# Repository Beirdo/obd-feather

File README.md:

# obd-feather
OBDII interface board with an attached Adafruit STM32F405 Feather Express.

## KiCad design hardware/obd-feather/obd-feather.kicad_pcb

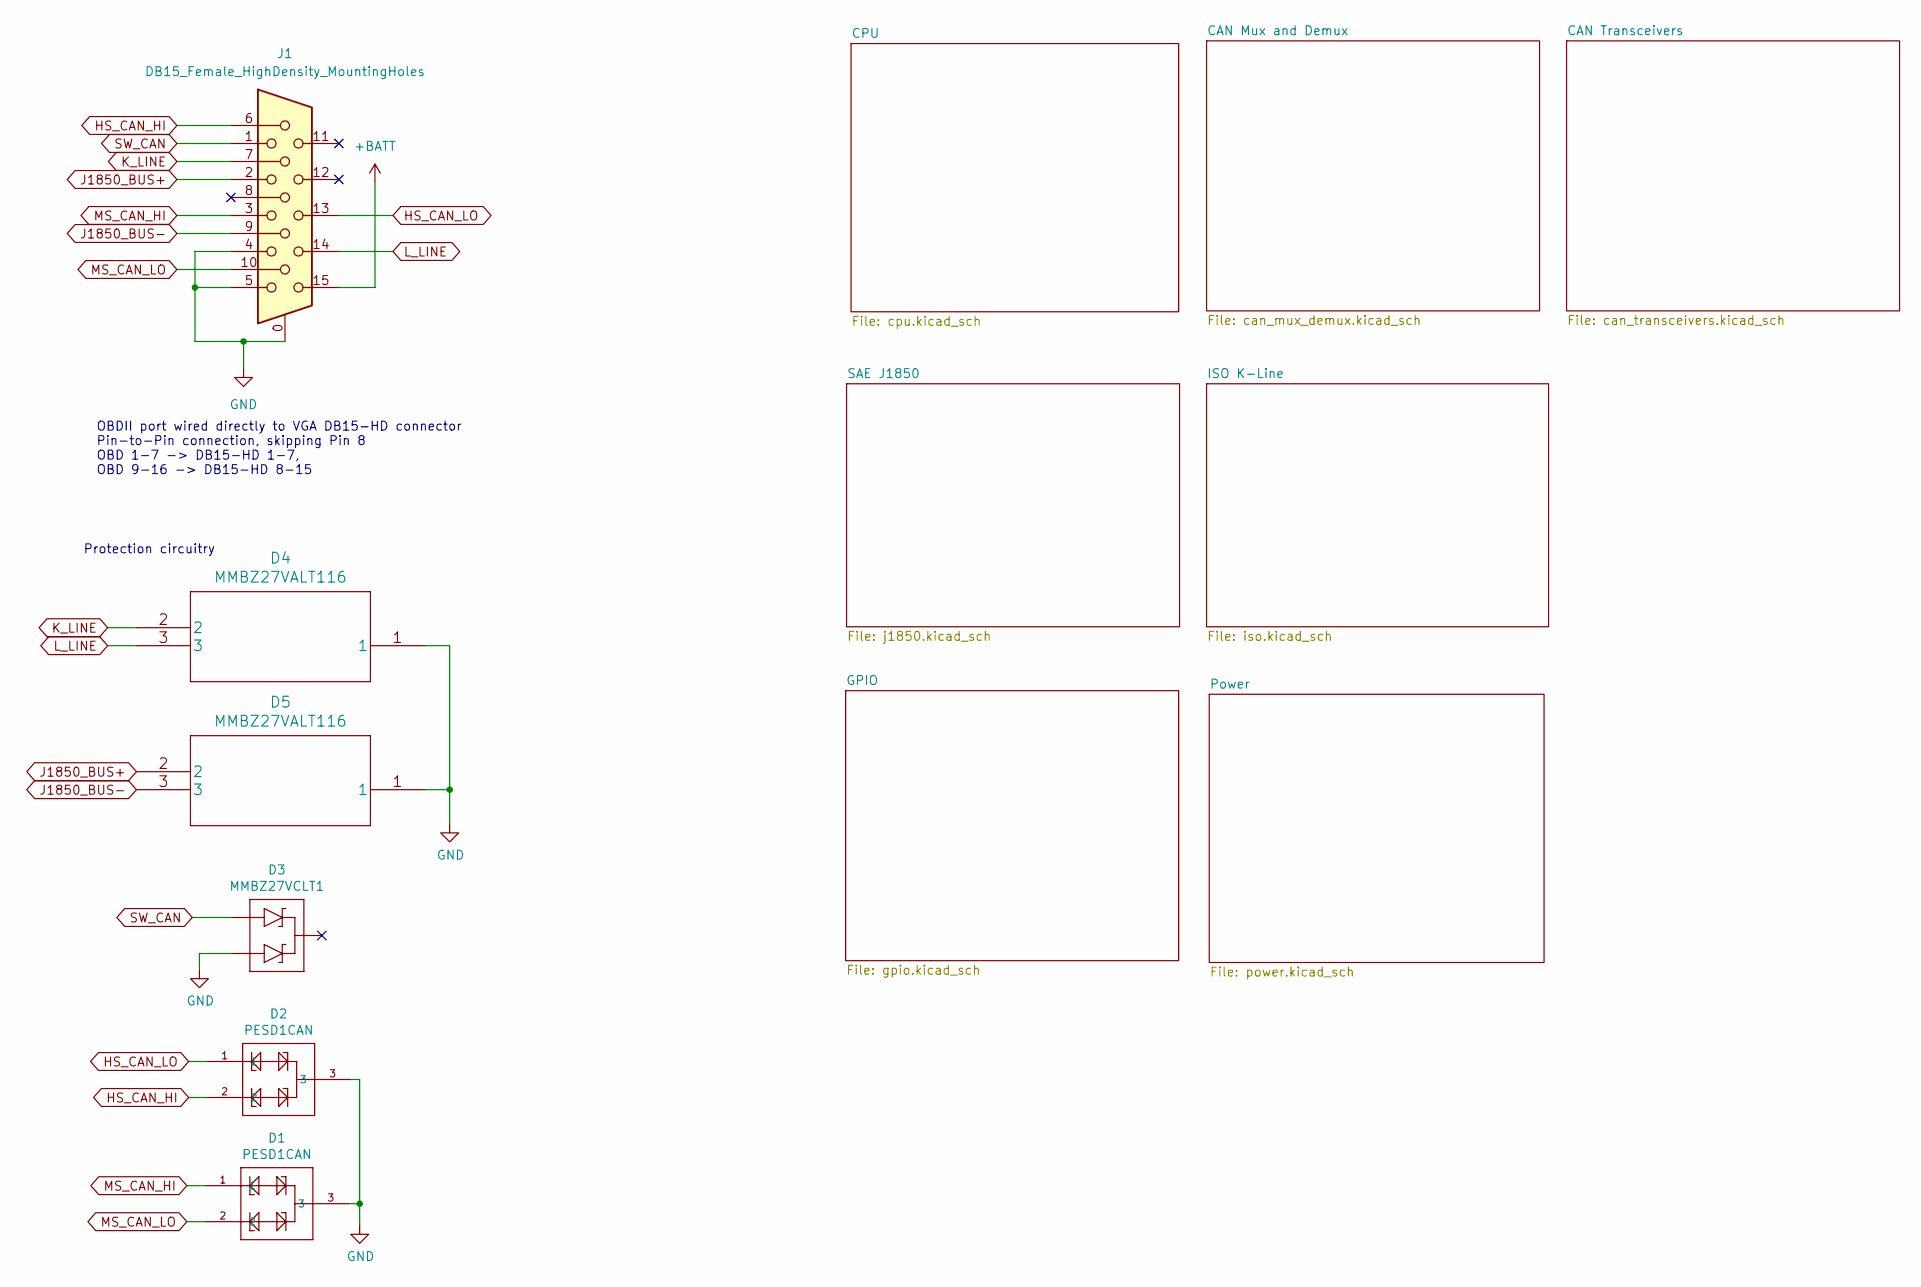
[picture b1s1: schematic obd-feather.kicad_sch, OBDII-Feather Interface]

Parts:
D1, D2: PESD1CAN; SOT23-3; Digikey 1727-3817-1-ND
D3: MMBZ27VCLT1; SOT23-3; Digikey MMBZ27VCL-FDICT-ND
D4, D5: MMBZ27VALT116; SOT23-3; Digikey MMBZ27VALT116CT-ND
J1: DB15_Female_HighDensity_MountingHoles; DSUB-15-HD_Female_Horizontal_P2.29x1.98mm_EdgePinOffset8.35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; Digikey L77HDE15SD1CH4FVGA-ND

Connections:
+BATT: J1.15; also elsewhere on the board
GND: D1.3, D2.3, D3.2 (A2), D4.1, D5.1, J1.0, J1.4, J1.5; also elsewhere on the board
HS_CAN_HI: D2.2, J1.6; also elsewhere on the board
HS_CAN_LO: D2.1, J1.13; also elsewhere on the board
J1850_BUS+: D5.2, J1.2; also elsewhere on the board
J1850_BUS-: D5.3, J1.9; also elsewhere on the board
K_LINE: D4.2, J1.7; also elsewhere on the board
L_LINE: D4.3, J1.14; also elsewhere on the board
MS_CAN_HI: D1.1, J1.3; also elsewhere on the board
MS_CAN_LO: D1.2, J1.10; also elsewhere on the board
SW_CAN: D3.1 (A1), J1.1; also elsewhere on the board

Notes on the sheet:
OBDII port wired directly to VGA DB15-HD connector Pin-to-Pin connection, skipping Pin 8 OBD 1-7 -> DB15-HD 1-7, OBD 9-16 -> DB15-HD 8-15
Protection circuitry

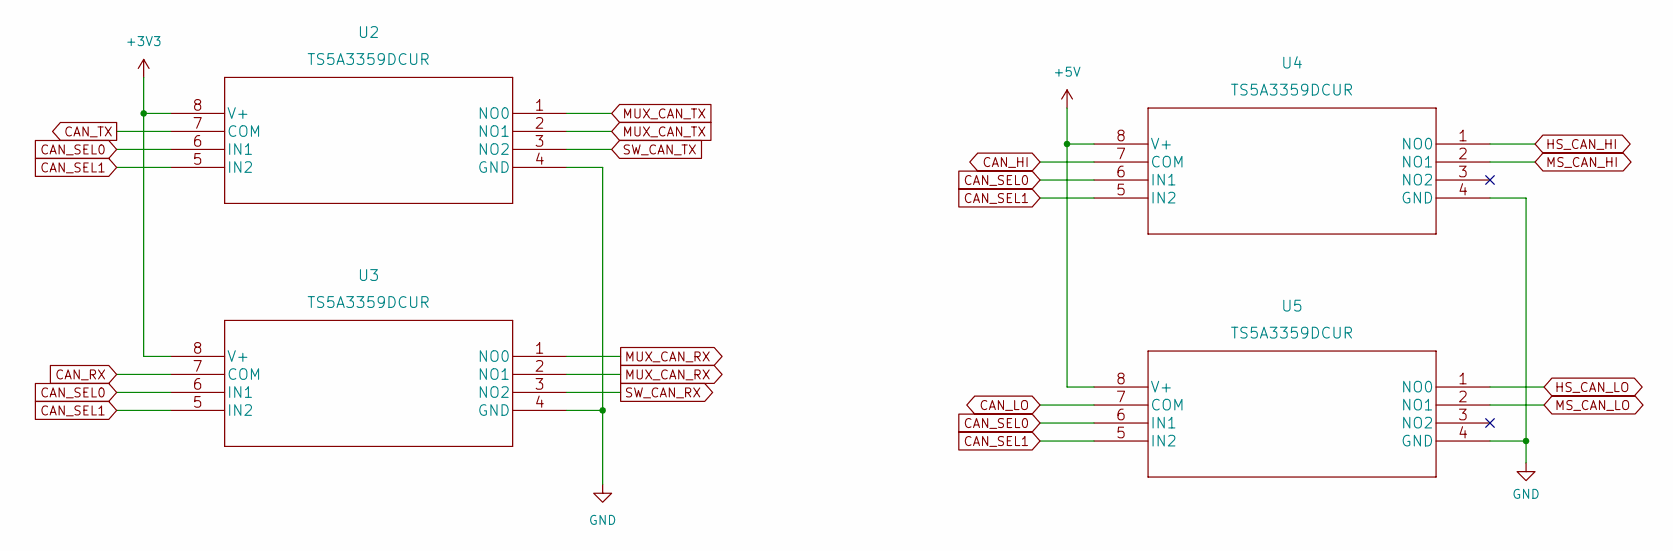
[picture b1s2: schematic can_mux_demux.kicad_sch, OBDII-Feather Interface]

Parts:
U2, U3, U4, U5: TS5A3359DCUR; Digikey 296-21193-1-ND

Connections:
+3V3: U2.8 (V+), U3.8 (V+); also elsewhere on the board
+5V: U4.8 (V+), U5.8 (V+); also elsewhere on the board
CAN_HI: U4.7 (COM); also elsewhere on the board
CAN_LO: U5.7 (COM); also elsewhere on the board
CAN_RX: U3.7 (COM); also elsewhere on the board
CAN_SEL0: U2.6 (IN1), U3.6 (IN1), U4.6 (IN1), U5.6 (IN1); also elsewhere on the board
CAN_SEL1: U2.5 (IN2), U3.5 (IN2), U4.5 (IN2), U5.5 (IN2); also elsewhere on the board
CAN_TX: U2.7 (COM); also elsewhere on the board
GND: U2.4 (GND), U3.4 (GND), U4.4 (GND), U5.4 (GND); also elsewhere on the board
HS_CAN_HI: U4.1 (NO0); also elsewhere on the board
HS_CAN_LO: U5.1 (NO0); also elsewhere on the board
MS_CAN_HI: U4.2 (NO1); also elsewhere on the board
MS_CAN_LO: U5.2 (NO1); also elsewhere on the board
MUX_CAN_RX: U3.1 (NO0), U3.2 (NO1); also elsewhere on the board
MUX_CAN_TX: U2.1 (NO0), U2.2 (NO1); also elsewhere on the board
SW_CAN_RX: U3.3 (NO2); also elsewhere on the board
SW_CAN_TX: U2.3 (NO2); also elsewhere on the board

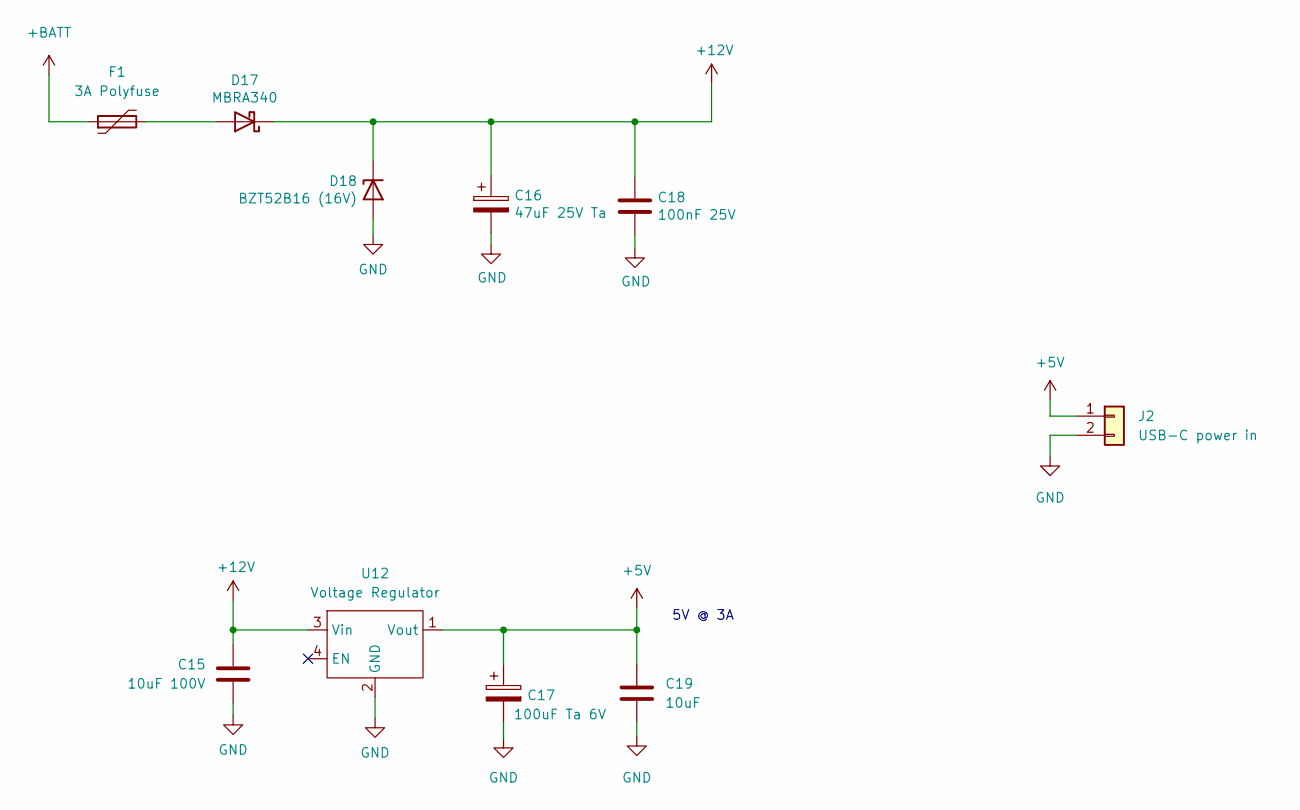
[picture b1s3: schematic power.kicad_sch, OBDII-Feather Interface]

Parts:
C15: 10uF 100V; C_1210_3225Metric_Pad1.33x2.70mm_HandSolder
C16: 47uF 25V Ta; CP_EIA-7343-31_Kemet-D_Pad2.25x2.55mm_HandSolder
C17: 100uF Ta 6V; CP_EIA-3216-10_Kemet-I_Pad1.58x1.35mm_HandSolder
C18: 100nF 25V; C_0805_2012Metric_Pad1.18x1.45mm_HandSolder
C19: 10uF; C_0805_2012Metric_Pad1.18x1.45mm_HandSolder
D17: MBRA340; D_SMA
D18: BZT52B16 (16V); D_SOD-123
F1: 3A Polyfuse; R_1812_4532Metric_Pad1.30x3.40mm_HandSolder; Digikey F2772CT-ND
J2: USB-C power in; PinHeader_1x02_P2.54mm_Vertical
U12: Voltage Regulator; Switching_Regulator_Module

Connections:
+5V: C17.1, C19.1, J2.1, U12.1 (Vout); also elsewhere on the board
+12V: C15.1, C16.1, C18.1, D17.1 (K), D18.1 (K), U12.3 (Vin); also elsewhere on the board
+BATT: F1.1; also elsewhere on the board
GND: C15.2, C16.2, C17.2, C18.2, C19.2, D18.2 (A), J2.2, U12.2 (GND); also elsewhere on the board
unnamed: D17.2 (A), F1.2

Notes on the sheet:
5V @ 3A

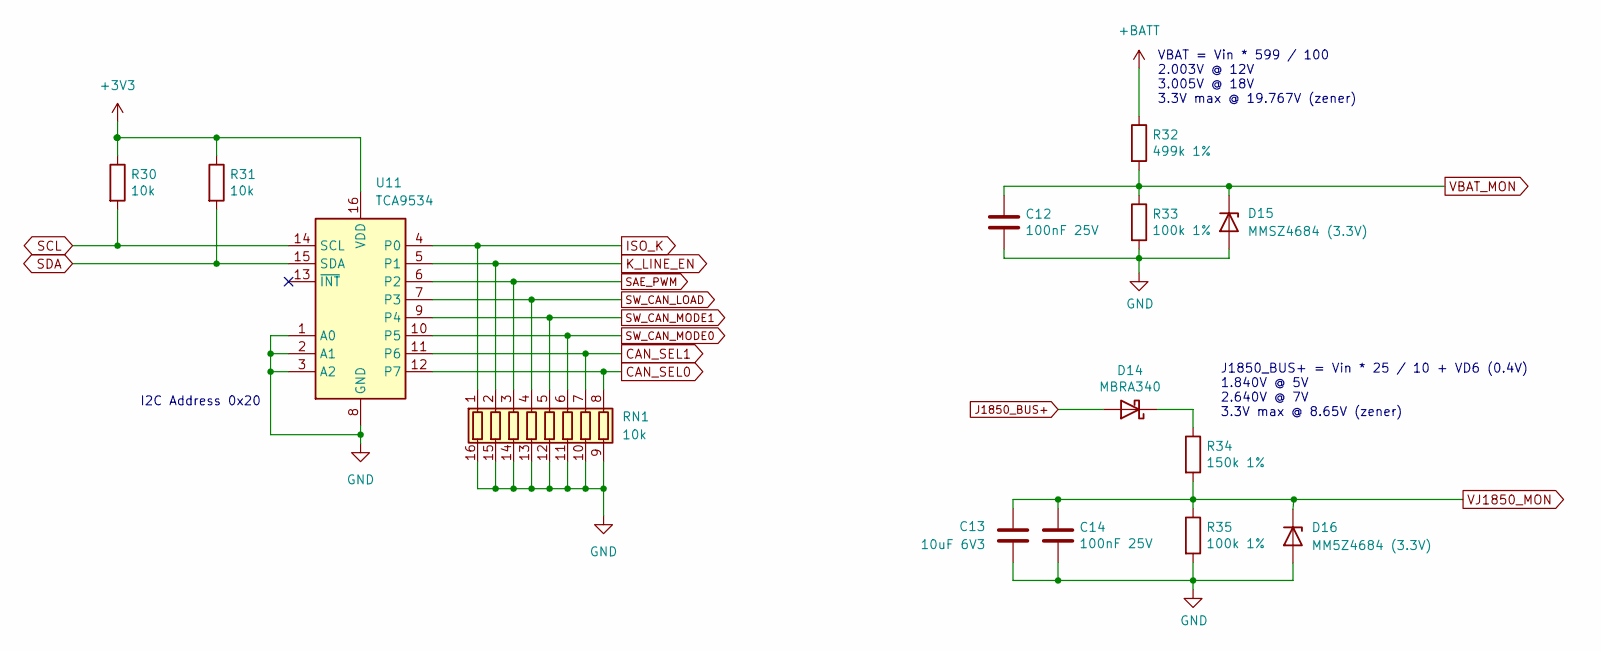
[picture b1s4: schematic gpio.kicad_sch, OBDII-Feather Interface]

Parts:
C12, C14: 100nF 25V; C_0805_2012Metric_Pad1.18x1.45mm_HandSolder
C13: 10uF 6V3; C_0805_2012Metric_Pad1.18x1.45mm_HandSolder
D14: MBRA340; D_SMA
D15: MMSZ4684 (3.3V); D_SOD-123
D16: MM5Z4684 (3.3V); D_SOD-123
R30, R31: 10k; R_0805_2012Metric_Pad1.20x1.40mm_HandSolder
R32: 499k 1%; R_0805_2012Metric_Pad1.20x1.40mm_HandSolder
R33, R35: 100k 1%; R_0805_2012Metric_Pad1.20x1.40mm_HandSolder
R34: 150k 1%; R_0805_2012Metric_Pad1.20x1.40mm_HandSolder
RN1: 10k; 742C163103JP
U11: TCA9534; TSSOP-16_4.4x5mm_P0.65mm

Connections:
+3V3: R30.1, R31.1, U11.16 (VDD); also elsewhere on the board
+BATT: R32.1; also elsewhere on the board
CAN_SEL0: RN1.8 (R8.1), U11.12 (P7); also elsewhere on the board
CAN_SEL1: RN1.7 (R7.1), U11.11 (P6); also elsewhere on the board
GND: C12.2, C13.1, C14.2, D15.2 (A), D16.2 (A), R33.2, R35.2, RN1.9 (R8.2), RN1.10 (R7.2), RN1.11 (R6.2), RN1.12 (R5.2), RN1.13 (R4.2), RN1.14 (R3.2), RN1.15 (R2.2), RN1.16 (R1.2), U11.1 (A0), U11.2 (A1), U11.3 (A2), U11.8 (GND); also elsewhere on the board
ISO_K: RN1.1 (R1.1), U11.4 (P0); also elsewhere on the board
J1850_BUS+: D14.2 (A); also elsewhere on the board
K_LINE_EN: RN1.2 (R2.1), U11.5 (P1); also elsewhere on the board
unnamed: D14.1 (K), R34.1
SAE_PWM: RN1.3 (R3.1), U11.6 (P2); also elsewhere on the board
SCL: R30.2, U11.14 (SCL); also elsewhere on the board
SDA: R31.2, U11.15 (SDA); also elsewhere on the board
SW_CAN_LOAD: RN1.4 (R4.1), U11.7 (P3); also elsewhere on the board
SW_CAN_MODE0: RN1.6 (R6.1), U11.10 (P5); also elsewhere on the board
SW_CAN_MODE1: RN1.5 (R5.1), U11.9 (P4); also elsewhere on the board
VBAT_MON: C12.1, D15.1 (K), R32.2, R33.1; also elsewhere on the board
VJ1850_MON: C13.2, C14.1, D16.1 (K), R34.2, R35.1; also elsewhere on the board

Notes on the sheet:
J1850_BUS+ = Vin * 25 / 10 + VD6 (0.4V) 1.840V @ 5V 2.640V @ 7V 3.3V max @ 8.65V (zener)
I2C Address 0x20
VBAT = Vin * 599 / 100 2.003V @ 12V 3.005V @ 18V 3.3V max @ 19.767V (zener)

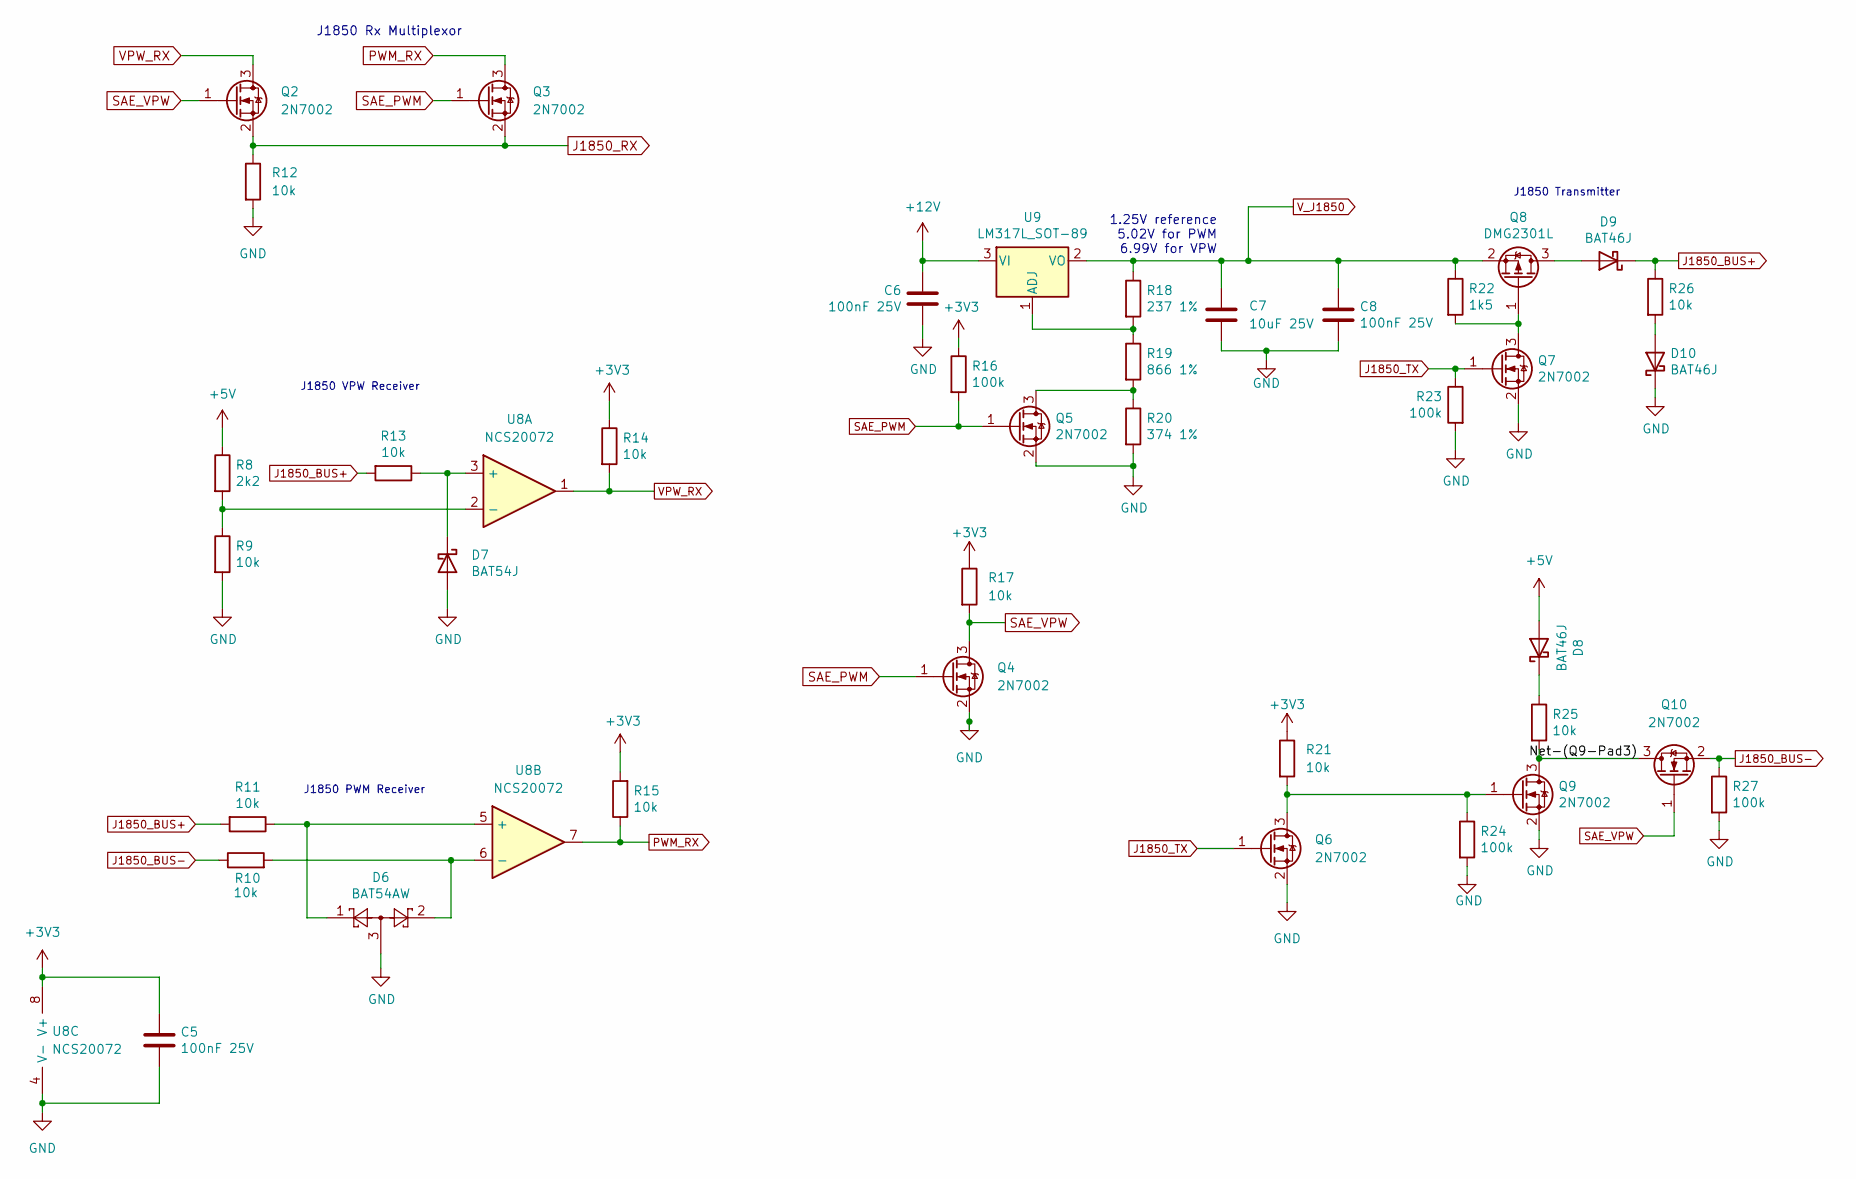
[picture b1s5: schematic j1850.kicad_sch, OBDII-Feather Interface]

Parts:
C5, C6, C8: 100nF 25V; C_0805_2012Metric_Pad1.18x1.45mm_HandSolder
C7: 10uF 25V; C_0805_2012Metric_Pad1.18x1.45mm_HandSolder
D6: BAT54AW; SOT-323_SC-70
D7: BAT54J; D_SOD-123
D8, D9, D10: BAT46J; D_SOD-123
Q2, Q3, Q4, Q5, Q6, Q7, Q9, Q10: 2N7002; SOT-23
Q8: DMG2301L; SOT-23
R8: 2k2; R_0805_2012Metric_Pad1.20x1.40mm_HandSolder
R9, R10, R11, R12, R13, R14, R15, R17, R21, R25, R26: 10k; R_0805_2012Metric_Pad1.20x1.40mm_HandSolder
R16, R23, R24, R27: 100k; R_0805_2012Metric_Pad1.20x1.40mm_HandSolder
R18: 237 1%; R_0805_2012Metric_Pad1.20x1.40mm_HandSolder
R19: 866 1%; R_0805_2012Metric_Pad1.20x1.40mm_HandSolder
R20: 374 1%; R_0805_2012Metric_Pad1.20x1.40mm_HandSolder
R22: 1k5; R_0805_2012Metric_Pad1.20x1.40mm_HandSolder
U8: NCS20072; TSSOP-8_4.4x3mm_P0.65mm
U9: LM317L_SOT-89; SOT-89-3

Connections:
+3V3: C5.2, R14.1, R15.2, R16.1, R17.1, R21.1, U8.8 (V+); also elsewhere on the board
+5V: D8.2 (A), R8.1; also elsewhere on the board
+12V: C6.2, U9.3 (VI); also elsewhere on the board
GND: C5.1, C6.1, C7.2, C8.2, D6.3, D7.2 (A), D10.1 (K), Q4.2 (S), Q5.2 (S), Q6.2 (S), Q7.2 (S), Q9.2 (S), R9.2, R12.2, R20.2, R23.2, R24.2, R27.2, U8.4 (V-); also elsewhere on the board
J1850_BUS+: D9.1 (K), R11.2, R13.2, R26.1; also elsewhere on the board
J1850_BUS-: Q10.2 (S), R10.1, R27.1; also elsewhere on the board
J1850_RX: Q2.2 (S), Q3.2 (S), R12.1; also elsewhere on the board
J1850_TX: Q6.1 (G), Q7.1 (G), R23.1; also elsewhere on the board
unnamed: D6.1, R11.1, U8.5 (+)
unnamed: D6.2, R10.2, U8.6 (-)
unnamed: D7.1 (K), R13.1, U8.3 (+)
unnamed: D8.1 (K), R25.1
unnamed: D9.2 (A), Q8.3 (D)
unnamed: D10.2 (A), R26.2
unnamed: Q5.3 (D), R19.2, R20.1
unnamed: Q6.3 (D), Q9.1 (G), R21.2, R24.1
unnamed: Q7.3 (D), Q8.1 (G), R22.2
unnamed: Q9.3 (D), Q10.3 (D), R25.2
unnamed: R8.2, R9.1, U8.2 (-)
unnamed: R18.2, R19.1, U9.1 (ADJ)
PWM_RX: Q3.3 (D), R15.1, U8.7
SAE_PWM: Q3.1 (G), Q4.1 (G), Q5.1 (G), R16.2; also elsewhere on the board
SAE_VPW: Q2.1 (G), Q4.3 (D), Q10.1 (G), R17.2
VPW_RX: Q2.3 (D), R14.2, U8.1
V_J1850: C7.1, C8.1, Q8.2 (S), R18.1, R22.1, U9.2 (VO)

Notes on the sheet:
J1850 Transmitter
J1850 Rx Multiplexor
J1850 VPW Receiver
J1850 PWM Receiver
1.25V reference 5.02V for PWM 6.99V for VPW

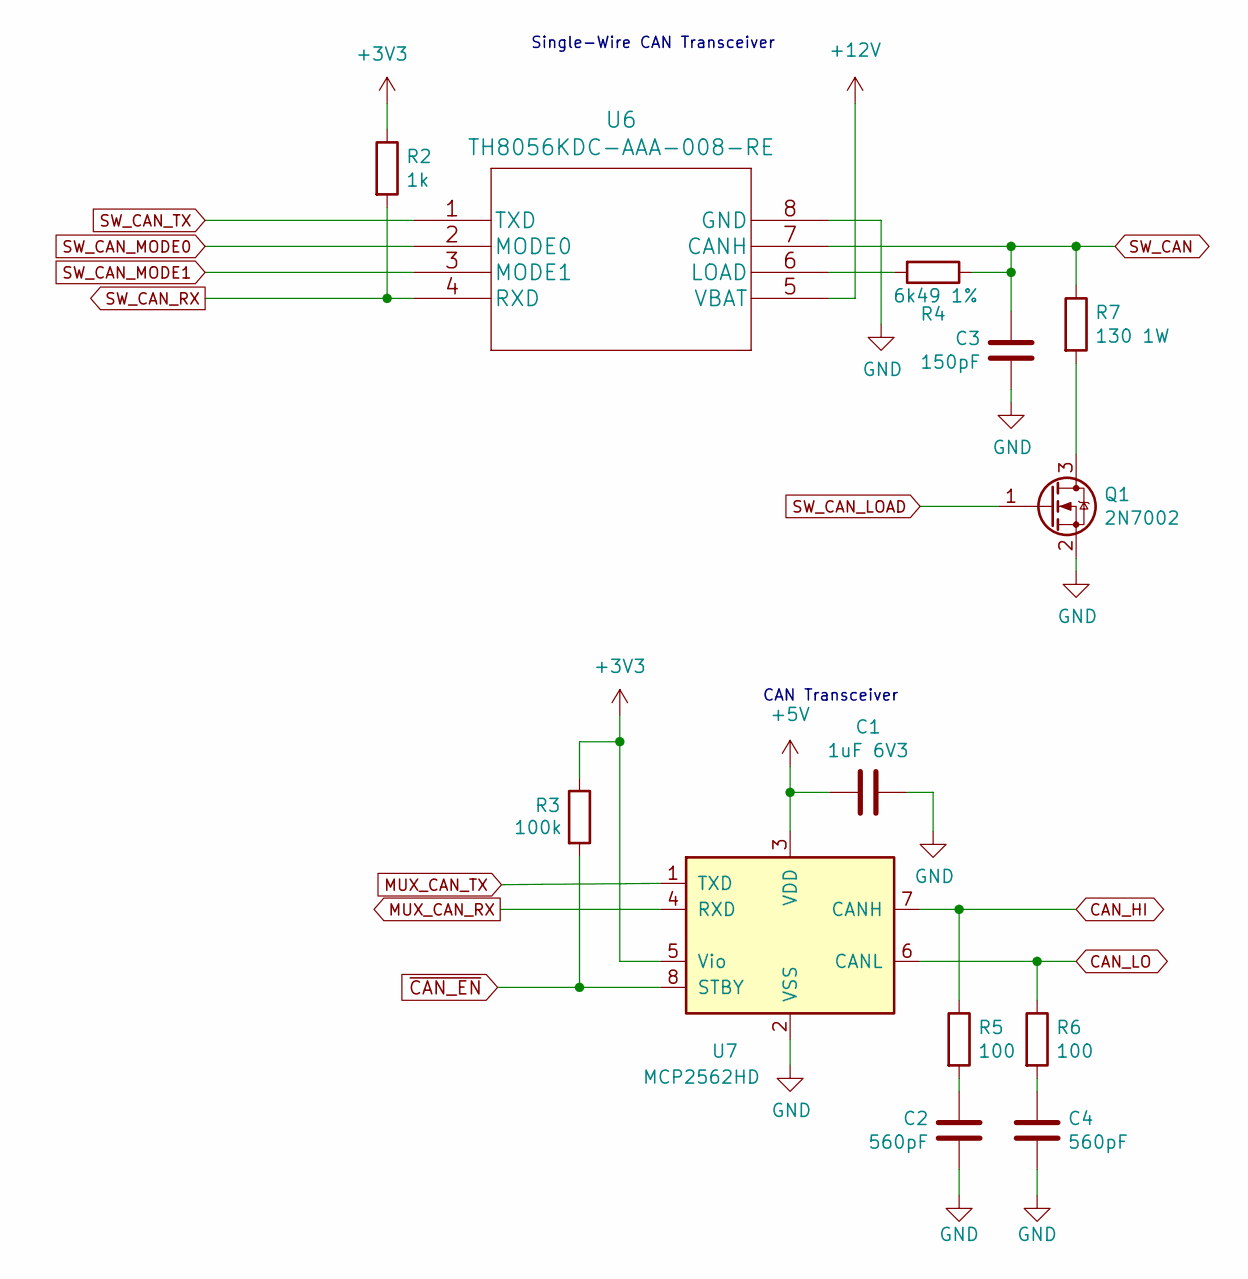
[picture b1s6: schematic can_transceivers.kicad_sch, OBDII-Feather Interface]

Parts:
C1: 1uF 6V3; C_0805_2012Metric_Pad1.18x1.45mm_HandSolder
C2, C4: 560pF; C_0805_2012Metric_Pad1.18x1.45mm_HandSolder
C3: 150pF; C_0805_2012Metric_Pad1.18x1.45mm_HandSolder
Q1: 2N7002; SOT-23
R2: 1k; R_0805_2012Metric_Pad1.20x1.40mm_HandSolder
R3: 100k; R_0805_2012Metric_Pad1.20x1.40mm_HandSolder
R4: 6k49 1%; R_0805_2012Metric_Pad1.20x1.40mm_HandSolder
R5, R6: 100; R_0805_2012Metric_Pad1.20x1.40mm_HandSolder
R7: 130 1W; R_2512_6332Metric_Pad1.40x3.35mm_HandSolder
U6: TH8056KDC-AAA-008-RE
U7: MCP2562HD; SOIC-8_3.9x4.9mm_P1.27mm

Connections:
+3V3: R2.1, R3.1, U7.5 (Vio); also elsewhere on the board
+5V: C1.2, U7.3 (VDD); also elsewhere on the board
+12V: U6.5 (VBAT); also elsewhere on the board
CAN_HI: R5.1, U7.7 (CANH); also elsewhere on the board
CAN_LO: R6.1, U7.6 (CANL); also elsewhere on the board
GND: C1.1, C2.1, C3.1, C4.2, Q1.2 (S), U6.8 (GND), U7.2 (VSS); also elsewhere on the board
MUX_CAN_RX: U7.4 (RXD); also elsewhere on the board
MUX_CAN_TX: U7.1 (TXD); also elsewhere on the board
unnamed: C2.2, R5.2
unnamed: C4.1, R6.2
unnamed: Q1.3 (D), R7.2
unnamed: R4.2, U6.6 (LOAD)
SW_CAN: C3.2, R4.1, R7.1, U6.7 (CANH); also elsewhere on the board
SW_CAN_LOAD: Q1.1 (G); also elsewhere on the board
SW_CAN_MODE0: U6.2 (MODE0); also elsewhere on the board
SW_CAN_MODE1: U6.3 (MODE1); also elsewhere on the board
SW_CAN_RX: R2.2, U6.4 (RXD); also elsewhere on the board
SW_CAN_TX: U6.1 (TXD); also elsewhere on the board
~CAN_EN: R3.2, U7.8 (STBY); also elsewhere on the board

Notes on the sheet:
CAN Transceiver
Single-Wire CAN Transceiver

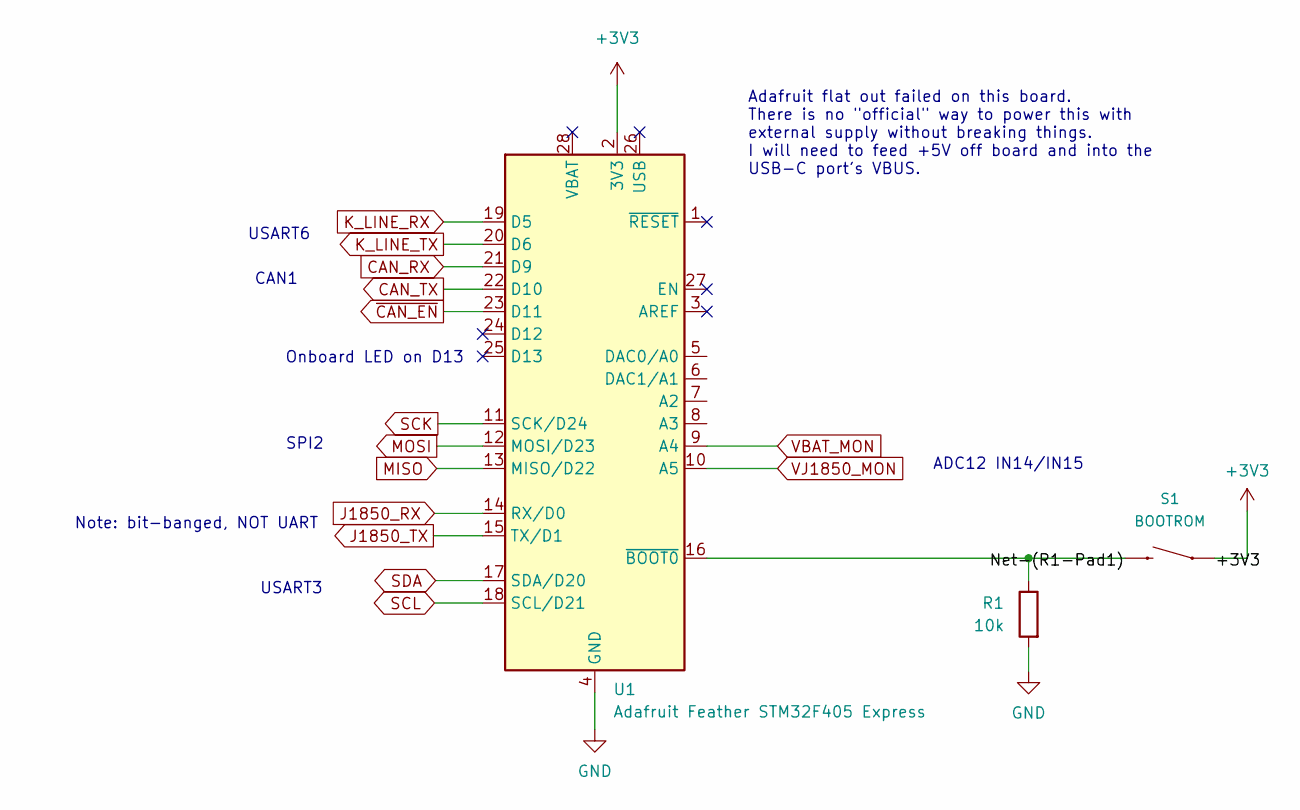
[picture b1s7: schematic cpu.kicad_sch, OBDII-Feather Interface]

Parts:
R1: 10k; R_0805_2012Metric_Pad1.20x1.40mm_HandSolder
S1: BOOTROM; TACTILE_SWITCH_PTH_6.0MM
U1: Adafruit Feather STM32F405 Express; Adafruit_Feather

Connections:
+3V3: S1.1, S1.2 (1), U1.2 (3V3); also elsewhere on the board
CAN_RX: U1.21 (D9); also elsewhere on the board
CAN_TX: U1.22 (D10); also elsewhere on the board
GND: R1.2, U1.4 (GND); also elsewhere on the board
J1850_RX: U1.14 (RX/D0); also elsewhere on the board
J1850_TX: U1.15 (TX/D1); also elsewhere on the board
K_LINE_RX: U1.19 (D5); also elsewhere on the board
K_LINE_TX: U1.20 (D6); also elsewhere on the board
MISO: U1.13 (MISO/D22)
MOSI: U1.12 (MOSI/D23)
SCK: U1.11 (SCK/D24)
SCL: U1.18 (SCL/D21); also elsewhere on the board
SDA: U1.17 (SDA/D20); also elsewhere on the board
VBAT_MON: U1.9 (A4); also elsewhere on the board
VJ1850_MON: U1.10 (A5); also elsewhere on the board
~CAN_EN: U1.23 (D11); also elsewhere on the board

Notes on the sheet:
Note: bit-banged, NOT UART
USART6
CAN1
Adafruit flat out failed on this board. There is no "official" way to power this with external supply without breaking things. I will need to feed +5V off board and into the USB-C port's VBUS.
USART3
SPI2
ADC12 IN14/IN15
Onboard LED on D13

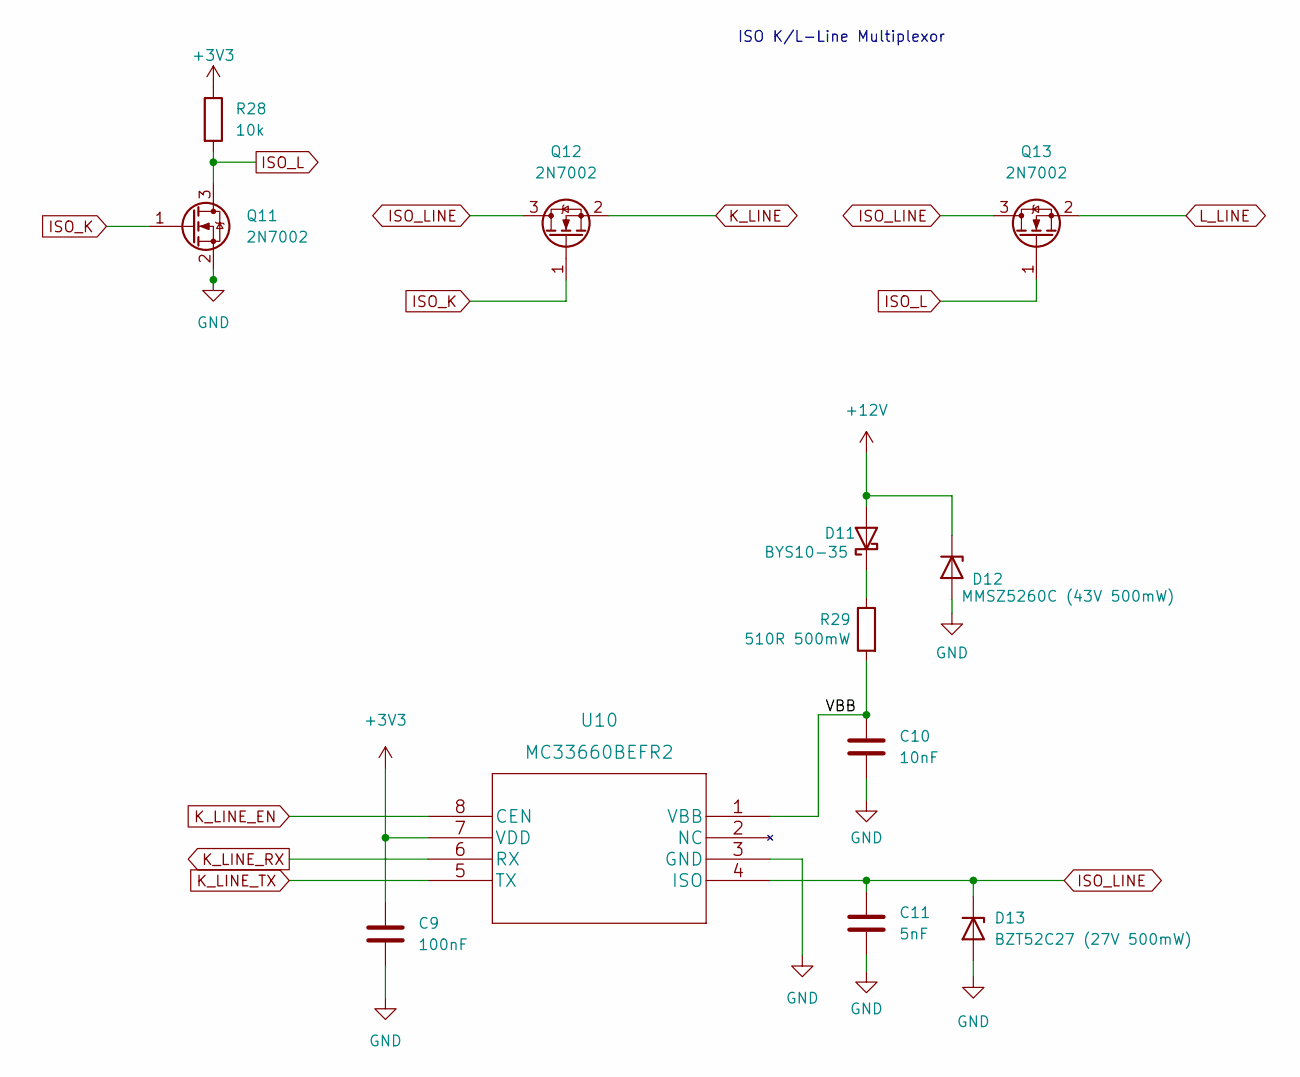
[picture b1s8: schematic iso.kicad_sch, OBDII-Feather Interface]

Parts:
C9: 100nF; C_0805_2012Metric_Pad1.18x1.45mm_HandSolder
C10: 10nF; C_0805_2012Metric_Pad1.18x1.45mm_HandSolder
C11: 5nF; C_0805_2012Metric_Pad1.18x1.45mm_HandSolder
D11: BYS10-35; D_SMA_Handsoldering
D12: MMSZ5260C (43V 500mW); D_SOD-123
D13: BZT52C27 (27V 500mW); D_SOD-123
Q11, Q12, Q13: 2N7002; SOT-23
R28: 10k; R_0805_2012Metric_Pad1.20x1.40mm_HandSolder
R29: 510R 500mW; R_1210_3225Metric_Pad1.30x2.65mm_HandSolder
U10: MC33660BEFR2

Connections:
+3V3: C9.1, R28.1, U10.7 (VDD); also elsewhere on the board
+12V: D11.2 (A), D12.1 (K); also elsewhere on the board
/ISO K-Line/VBB: C10.1, R29.2, U10.1 (VBB)
GND: C9.2, C10.2, C11.2, D12.2 (A), D13.2 (A), Q11.2 (S), U10.3 (GND); also elsewhere on the board
ISO_K: Q11.1 (G), Q12.1 (G); also elsewhere on the board
ISO_L: Q11.3 (D), Q13.1 (G), R28.2
ISO_LINE: C11.1, D13.1 (K), Q12.3 (D), Q13.3 (D), U10.4 (ISO)
K_LINE: Q12.2 (S); also elsewhere on the board
K_LINE_EN: U10.8 (CEN); also elsewhere on the board
K_LINE_RX: U10.6 (RX); also elsewhere on the board
K_LINE_TX: U10.5 (TX); also elsewhere on the board
L_LINE: Q13.2 (S); also elsewhere on the board
unnamed: D11.1 (K), R29.1

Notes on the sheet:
ISO K/L-Line Multiplexor

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
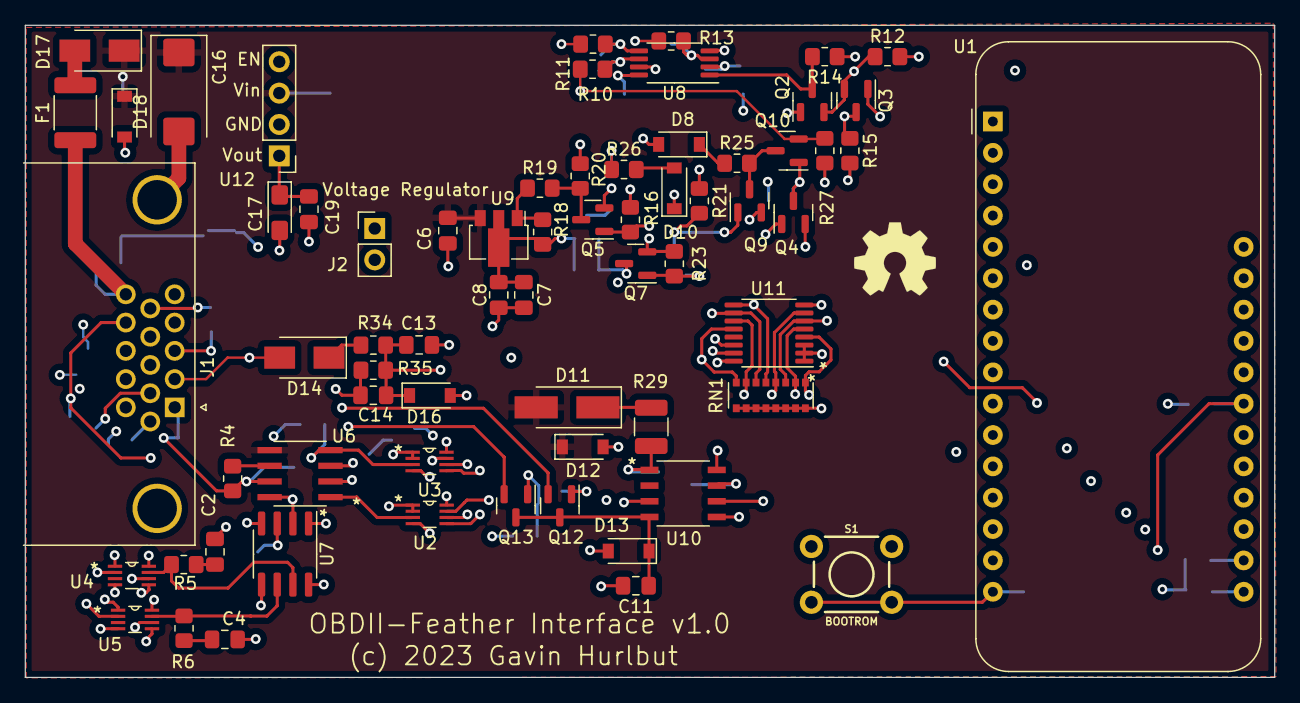
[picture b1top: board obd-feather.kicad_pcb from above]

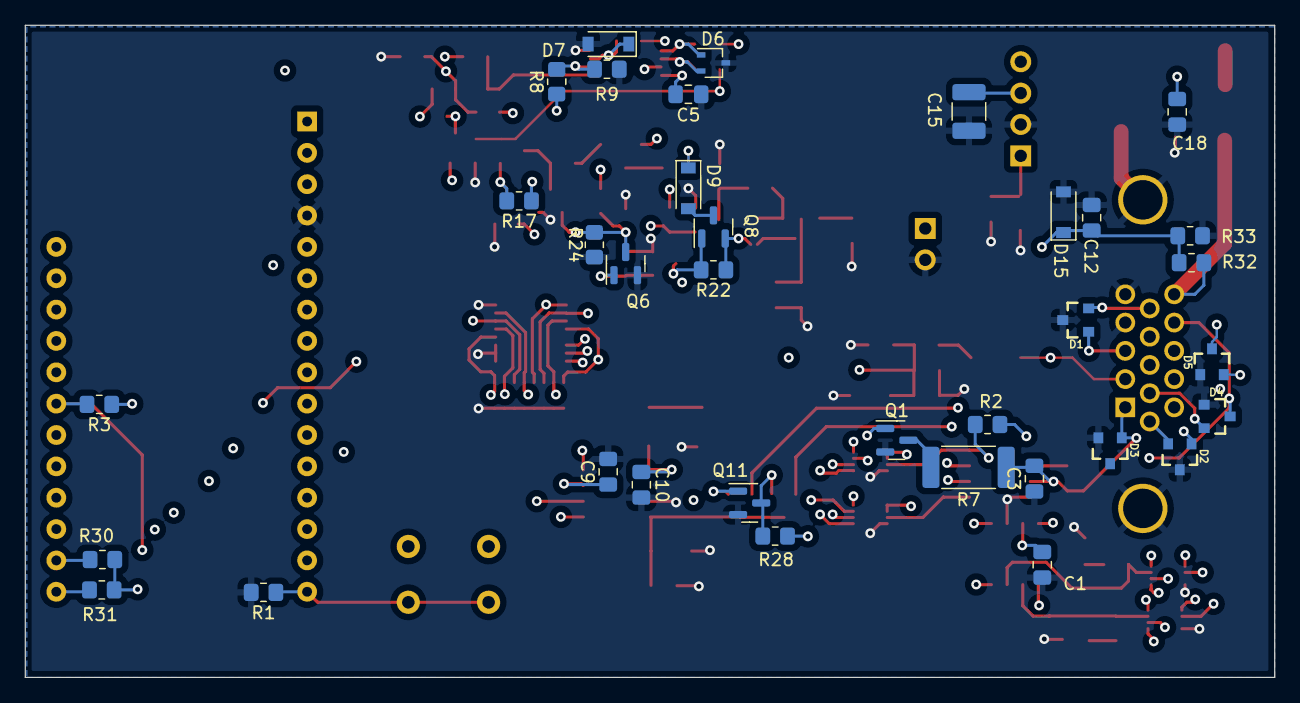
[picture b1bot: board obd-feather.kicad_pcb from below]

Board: 4 copper layers, 101.2 x 52.8 mm, 102 parts (35 on the bottom side), 66 nets.

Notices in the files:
hardware/obd-feather/obd-feather.kicad_pcb:
(c) 2023 Gavin Hurlbut
parts and their libraries:
Copyright 2021 Accelerated Designs. All rights reserved.
